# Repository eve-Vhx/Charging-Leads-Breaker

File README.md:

# Charging-Leads-Breaker
PCB design and code for I2C-controlled circuit breaker

Latest PCB Design CAA 6/21/2024 1615hrs: "eve PCB Project (Via Spam)"

Panelization of PCB Design: "eve PCB Project"

Latest I2C Test Code CAA 6/21/2024 1615hrs: "smbus2 Test Code"

Documentation can be found [here](https://docs.google.com/document/d/1M2C9KjVvsc9MSWZB_28-PoXH00KxS9CfH0Og3sLEewM/edit?usp=sharing).

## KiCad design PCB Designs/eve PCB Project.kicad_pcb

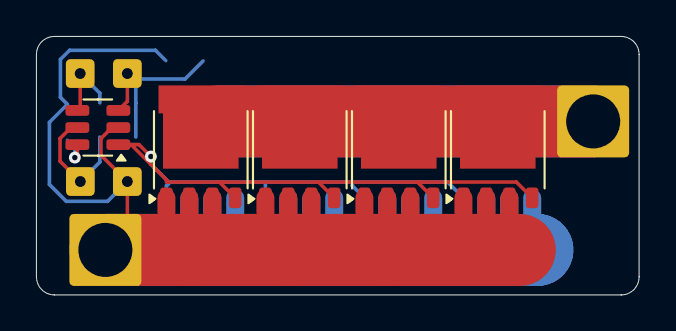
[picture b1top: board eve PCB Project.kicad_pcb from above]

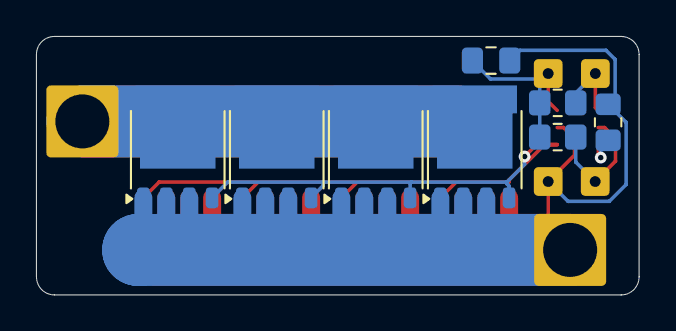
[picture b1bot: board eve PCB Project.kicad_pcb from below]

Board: 2 copper layers, 33.5 x 14.4 mm, 19 parts (8 on the bottom side), 7 nets.

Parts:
+5V: Conn_01x01_Socket; SolderWire-0.1sqmm_1x01_D0.4mm_OD1mm
C1: 0.1uF; C_0805_2012Metric_Pad1.18x1.45mm_HandSolder
GND: Conn_01x01_Socket; SolderWire-2.5sqmm_1x01_D2.4mm_OD3.6mm
GND#2: Conn_01x01_Socket; SolderWire-0.1sqmm_1x01_D0.4mm_OD1mm
Lead (-): Conn_01x01_Socket; SolderWire-2.5sqmm_1x01_D2.4mm_OD3.6mm
Q1, Q2, Q3, Q4: 5R2L60; LFPAK56
Q5, Q6, Q7, Q8: PSMN5R2-60YL; LFPAK56
R1: 10k; R_0805_2012Metric_Pad1.20x1.40mm_HandSolder
R2, R3: 4.7k; R_0805_2012Metric_Pad1.20x1.40mm_HandSolder
SCL: Conn_01x01_Socket; SolderWire-0.1sqmm_1x01_D0.4mm_OD1mm
SDA: Conn_01x01_Socket; SolderWire-0.1sqmm_1x01_D0.4mm_OD1mm
U1: MCP4725; SOT-23-6

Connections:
+5V: +5V.1, C1.1, R2.1, R3.1, U1.3 (VDD)
GND: C1.2, GND.1, GND#2.1, Q1.1 (S), Q1.2 (S), Q1.3 (S), Q2.1 (S), Q2.2 (S), Q2.3 (S), Q3.1 (S), Q3.2 (S), Q3.3 (S), Q4.1 (S), Q4.2 (S), Q4.3 (S), Q5.1 (S), Q5.2 (S), Q5.3 (S), Q6.1 (S), Q6.2 (S), Q6.3 (S), Q7.1 (S), Q7.2 (S), Q7.3 (S), Q8.1 (S), Q8.2 (S), Q8.3 (S), R1.2, U1.2 (VSS)
Lead (-): Lead (-).1, Q1.5 (D), Q2.5 (D), Q3.5 (D), Q4.5 (D), Q5.5 (D), Q6.5 (D), Q7.5 (D), Q8.5 (D)
unnamed: Q1.4 (G), Q2.4 (G), Q3.4 (G), Q4.4 (G), Q5.4 (G), Q6.4 (G), Q7.4 (G), Q8.4 (G), U1.1 (VOUT)
unnamed: R1.1, U1.6 (A0)
SCL: R2.2, SCL.1, U1.5 (SCL)
SDA: R3.2, SDA.1, U1.4 (SDA)

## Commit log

2024-05-24 Create hi
2024-05-24 Create g
2024-06-14 Create Files
2024-06-14 Create file
2024-06-21 Update smbus2 Test Code after testing on ARK Jetson
